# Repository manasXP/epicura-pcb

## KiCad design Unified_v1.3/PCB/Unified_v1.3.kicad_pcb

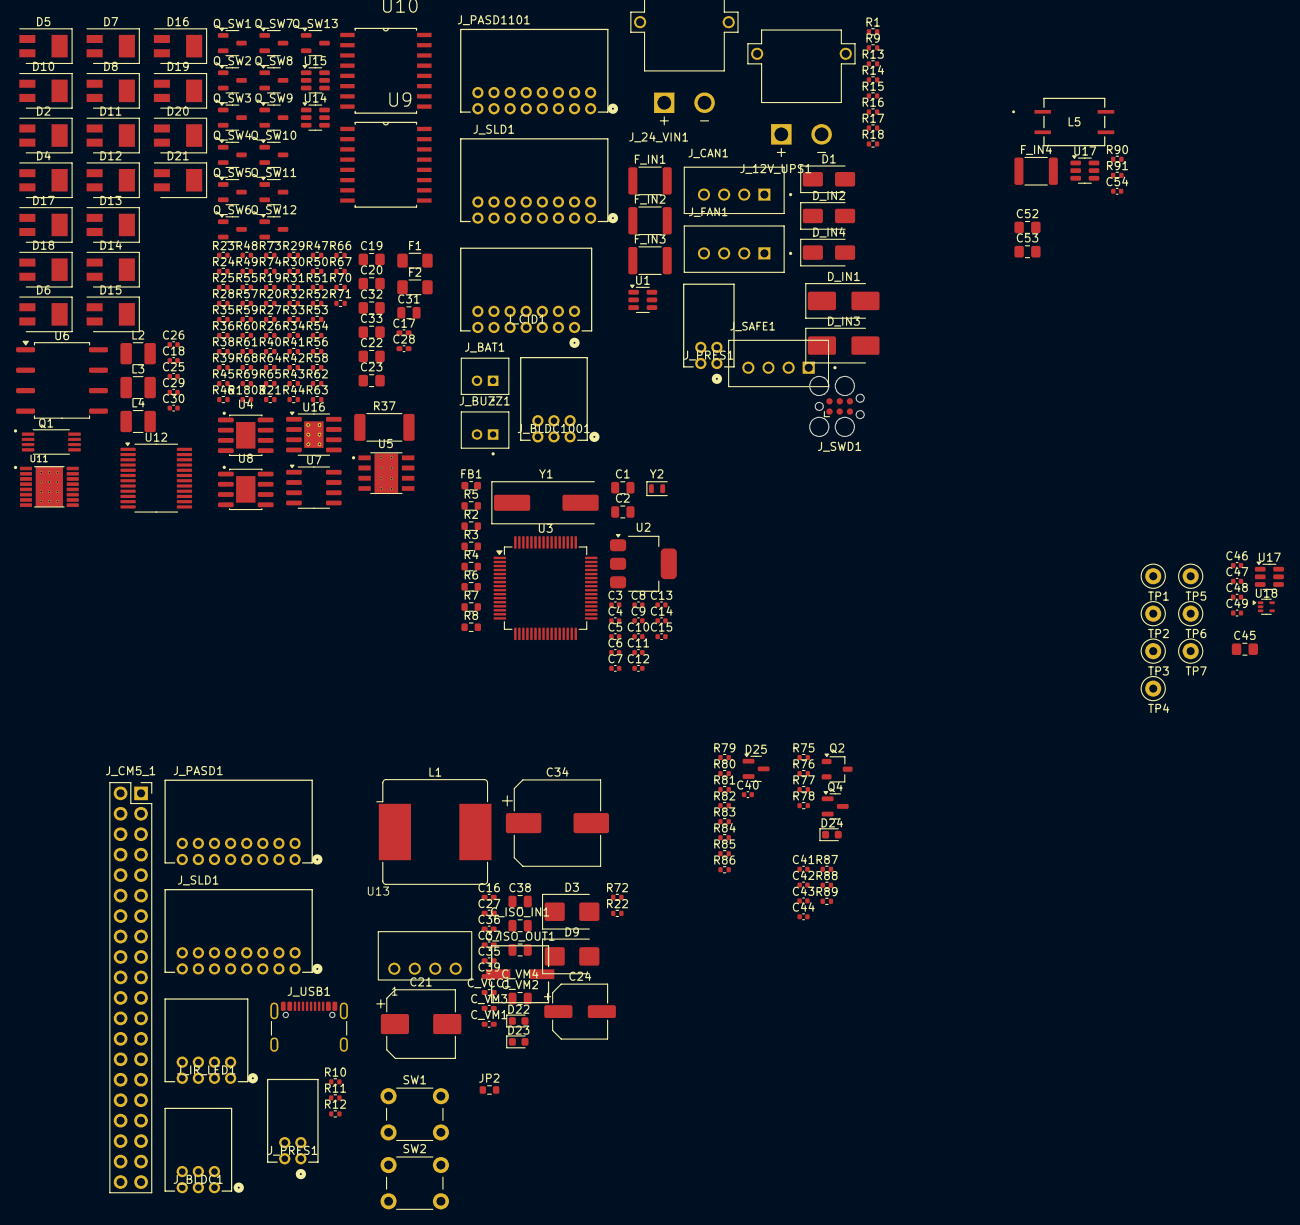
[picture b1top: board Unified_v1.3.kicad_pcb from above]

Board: 4 copper layers, 259 parts (0 on the bottom side), 185 nets, no tracks yet.

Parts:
C1, C2, C31: 10uF; C_0805_2012Metric
C3, C4, C5, C6, C7, C8, C9, C15, C29, C30, C40, C41, C42, C43, C54: 100nF; C_0402_1005Metric
C10: 1uF; C_0402_1005Metric
C11, C12: 18pF; C_0402_1005Metric
C13, C14: 6.8pF; C_0402_1005Metric
C16, C17, C27, C28, C35, C36, C37, C39: 100nF; C_0402_1005Metric_Pad0.74x0.62mm_HandSolder
C18: 2.2nF; C_0402_1005Metric
C19, C20, C32, C33, C45: 22uF@25V; C_0805_2012Metric_Pad1.18x1.45mm_HandSolder
C21: 100uF@25V; CP_Elec_8x10
C22, C23: 22uF@10V; C_0805_2012Metric_Pad1.18x1.45mm_HandSolder
C24: 220uF@10V; CP_Elec_6.3x7.7
C25: 22pF; C_0402_1005Metric
C26: 10nF; C_0402_1005Metric
C34: 470uF@35V; CP_Elec_10x12.5
C38: 22uF@16V; C_0805_2012Metric
C44: 4.7uF; C_0402_1005Metric
C46, C47, C48, C49: 100pF; C_0402_1005Metric
C52, C53: 10uF@50V; C_0805_2012Metric_Pad1.18x1.45mm_HandSolder
C_ISO_IN1: 4.7uF@16V; C_0805_2012Metric
C_ISO_OUT1: 10uF@16V; C_0805_2012Metric
C_VCC1: 100nF; C_0402_1005Metric_Pad0.74x0.62mm_HandSolder
C_VM1, C_VM3: 100nF; C_0402_1005Metric_Pad0.74x0.62mm_HandSolder
C_VM2: 10uF; C_0805_2012Metric
C_VM4: 100uF; 100uF_Wruth_CAP_WCAP-ASLI_06p3X07p7_WRE
D1: SS54; D_SMA
D2, D6, D7, D8, D11, D12, D13, D14, D15, D16, D17, D18, D19, D20, D21: SS14; D_SMB_Modified
D3: SMBJ12A; D_SMB
D4, D5, D10: SS34; D_SMB_Modified
D9: SMBJ6.5A; D_SMB
D22: LED_BLUE_STBY; D_0603_1608Metric
D23: LED_RED_CHRG; D_0603_1608Metric
D24: LED_GREEN_Status; D_0603_1608Metric
D25: CDSOT23-SM712; SOT-23
D_IN1, D_IN3: SMBJ24A _ 39.2 V; D_SMB_Handsoldering
D_IN2, D_IN4: SS54; D_SMA
F1, F2: 1.5A; R_1206_3216Metric_Pad1.30x1.75mm_HandSolder
FB1: 600R@100MHz; L_0603_1608Metric
F_IN1, F_IN2, F_IN4: 5A_PTC; R_1812_4532Metric
F_IN3: 500mA; R_1812_4532Metric
JP2: SWO_Jumper; R_0603_1608Metric
J_12V_UPS1, J_24_VIN1: XT30PW-M; AMASS_XT30PW-M
J_BAT1: B2B-PH-K-S; JST_B2B-PH-K-S
J_BLDC1, J_BLDC1001: DF11-6DP-2DS; CON6_2X3_RF_DF11
J_BUZZ1: B2B-PH-K-S; JST_B2B-PH-K-S
J_CAN1: B4B-XH-A; JST_B4B-XH-A
J_CID1: DF11-14DP-2DS; CON14_2X7_RF_DF11_HIR
J_CM5_1: Conn_02x20_Odd_Even; PinSocket_2x20_P2.54mm_Vertical
J_FAN1: B4B-XH-A; JST_B4B-XH-A
J_IR_LED1: DF11-8DP-2DS; CON8_2X4_RF_DF11
J_PASD1, J_PASD1101: DF11-16DP-2DS; CON16_2X8_RF_DF11
J_PRES1, J_PRES1#2: DF11-4DP-2DS; CON4_2X2_RF_DF11_HIR
J_SAFE1: B4B-XH-A; JST_B4B-XH-A
J_SLD1, J_SLD1#2: DF11-16DP-2DS; CON16_2X8_RF_DF11
J_SWD1: Conn_ARM_SWD_TagConnect_TC2030; Tag-Connect_TC2030-IDC-FP_2x03_P1.27mm_Vertical
J_USB1: USB_C_Receptacle_USB2.0_16P; USB_C_Receptacle_GCT_USB4105-xx-A_16P_TopMnt_Horizontal
L1: 10uH; L_Bourns_SRR1208_12.7x12.7mm
L2, L4: 33uH; L_1210_3225Metric_Pad1.42x2.65mm_HandSolder
L3: 22uH; L_1210_3225Metric_Pad1.42x2.65mm_HandSolder
L5: DR331-513AEE; IND_DR331-513AEE_BRN
Q1: FS8205A; FS8205A_SOP65P640X120-8N
Q2: SI2301-TP; TSOT-23
Q4: 2N7002; SOT-23
Q_SW1: 2N7002; SOT-23-3
Q_SW2, Q_SW3, Q_SW4, Q_SW5, Q_SW6, Q_SW7, Q_SW8, Q_SW9, Q_SW10, Q_SW11, Q_SW12, Q_SW13: IRLML6344; SOT-23-3
R1, R17, R18, R23, R28, R35, R39, R55, R65: 100K; R_0402_1005Metric
R2, R3: 4K7; R_0603_1608Metric
R4, R5, R6, R7, R8: 10K; R_0603_1608Metric
R9, R22, R27, R30, R32, R34, R38, R42, R44, R45, R50, R52, R54, R58, R63, R67, R71, R75, R77, R87, R88, R89, R90: 10K; R_0402_1005Metric
R10, R11, R12, R21, R29, R31, R33, R41, R43, R46, R47, R49, R51, R53, R56, R57, R59, R60, R61, R62, R66, R70, R72, R76, R79, R80, R81, R82, R83, R84, R85, R86, R91: 100R; R_0402_1005Metric
R13, R14: 5.1K; R_0402_1005Metric
R15, R16: 22R; R_0402_1005Metric
R19: 140K; R_0402_1005Metric
R20: 52.3K; R_0402_1005Metric
R24: 140KOhms; R_0402_1005Metric
R25: 10KOhms; R_0402_1005Metric
R26: 37.4K; R_0402_1005Metric
R36: 71.5K; R_0402_1005Metric
R37: 33m@3W; R_2512_6332Metric_Pad1.40x3.35mm_HandSolder
R40: 120R; R_0402_1005Metric
R48, R68, R69, R73: 1K; R_0402_1005Metric
R64: 732K; R_0402_1005Metric
R74, R1803: 2K; R_0402_1005Metric
R78: 330R; R_0402_1005Metric
SW1, SW2: SW_Push; SW_PUSH_6mm
TP1: PA2; TestPoint_Loop_D1.80mm_Drill1.0mm_Beaded
TP2: PA7; TestPoint_Loop_D1.80mm_Drill1.0mm_Beaded
TP3: PA9; TestPoint_Loop_D1.80mm_Drill1.0mm_Beaded
TP4: PC0; TestPoint_Loop_D1.80mm_Drill1.0mm_Beaded
TP5: PC1; TestPoint_Loop_D1.80mm_Drill1.0mm_Beaded
TP6: PC5; TestPoint_Loop_D1.80mm_Drill1.0mm_Beaded
TP7: PC13; TestPoint_Loop_D1.80mm_Drill1.0mm_Beaded
U1, U17: USBLC6-2SC6; SOT-23-6
U2: AMS1117-3.3; SOT-223-3_TabPin2
U3: STM32G474RETx; LQFP-64_10x10mm_P0.5mm
U4, U8: MP1584EN; MP1584EN_SOIC127P600X170-9N
U5: TPS54531DDA; TPS54531DDA_VREG_LM5017MR_NOPB
U6: ISO1050DUB; SOP-8_6.62x9.15mm_P2.54mm
U7: INA219AxD; SOIC-8_3.9x4.9mm_P1.27mm
U9, U10: PCF8574AT; SOIC127P1032X265-16N_PCF8574AT
U11: DRV8876PWPR
U12: TB6612FNG; SSOP-24_5.3x8.2mm_P0.65mm
U13: B0505S-1WR3; B0505S-1WR3_Footprint
U14: MT3608; SOT-23-6
U15: DW01A; SOT-23-6
U16: TP4056-42-ESOP8; SOIC-8-1EP_3.9x4.9mm_P1.27mm_EP2.41x3.3mm_ThermalVias
U17#2: TXB0101DBV; SOT-23-6
U18: TPD3E001DRLR; SOT-553
Y1: 8MHz; Crystal_SMD_HC49-SD
Y2: 32.768kHz; Crystal_SMD_2012-2Pin_2.0x1.2mm

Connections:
/24V_Divider: R1.2, R9.1, U3.13 (PA1)
/+3V3_OUT: C2.1, C3.1, C4.1, C5.1, C6.1, C7.1, C8.1, C27.2, C29.2, C35.2, C36.2, C37.1, C44.1, C54.2, C_VCC1.2, FB1.1, J_IR_LED1.3, J_PRES1.3, J_PRES1#2.3, J_SLD1#2.11, J_SWD1.1 (VCC), R2.1, R3.1, R5.1, R6.1, R7.2, R8.2, R45.2, R55.2, R86.1, R87.1, R88.1, R89.1, SW1.2, U2.2 (VO), U3.1 (VBAT), U3.16 (VDD), U3.32 (VDD), U3.48 (VDD), U3.64 (VDD), U6.1 (VCC1), U7.5 (VS), U9.1 (A0), U9.16 (VDD), U10.16 (VDD), U11.5 (VREF), U12.20 (VCC), U17.5 (VBUS), U17#2.1 (V_{CCA}), U18.5
/+5V_Detect: R17.1, R18.2, U3.17 (PA3)
/+5V_LED_RING: J_IR_LED1.7, Q2.3 (D), U17#2.6 (V_{CCB})
/+5V_Merger: C1.1, C_ISO_IN1.1, D1.1 (K), D2.1 (K), D18.1 (K), F_IN4.1, J_BUZZ1.1, Q2.2 (S), R75.1, U1.5 (VBUS), U2.3 (VI), U13.2 (Vin)
/+5V_USB: D1.2 (A), F_IN3.1, R17.2, R68.2, R69.1, U16.4 (V_{CC}), U16.8 (CE)
/+12V_IN: C45.1, D_IN3.1 (A1), D_IN4.1 (K), R19.1, U5.2 (VIN)
/+12V_Rail: C_VM1.2, C_VM2.2, C_VM3.2, C_VM4.1, D3.1 (K), F1.2, J_FAN1.1, J_FAN1.3, J_PASD1.1, J_PASD1.3, J_PASD1.5, J_PASD1.7, J_PASD1.9, J_PASD1.11, J_PASD1.13, J_SLD1#2.5, J_SLD1#2.7, U11.11 (VM), U12.13 (VM2), U12.14 (VM3), U12.24 (VM1)
/+24V_CC: C52.1, C53.1, J_CID1.12, R23.1, R35.1, R37.2, U4.7 (VIN), U7.7 (IN-), U8.7 (VIN)
/+24V_VIN: D_IN1.1 (A1), D_IN2.1 (K), J_BLDC1.1, R1.1, R37.1, U7.8 (IN+)
/BAT+: J_BAT1.1, L4.1, R72.2, R1803.1, U14.4 (EN), U14.5 (IN), U16.5 (BAT)
/BAT-: C39.1, J_BAT1.2, Q1.2, Q1.3, U15.6 (GND)
/BUZZ1_OUT: J_BUZZ1.2, Q_SW1.3 (D)
/CAN_H: L5.1, R40.2, U6.7 (CANH)
/CAN_L: L5.2, R40.1, U6.6 (CANL)
/CID1_EN: R12.1, U10.12 (P7)
/CID2_OUT1: J_CID1.7, U11.8 (OUT1)
/CID2_OUT2: J_CID1.8, U11.10 (OUT2)
/CM5_DE: JP2.2 (B), R91.2, U3.56 (PB3)
/Connector/12V_IN: J_PASD1101.1, J_PASD1101.3, J_PASD1101.5, J_PASD1101.7, J_PASD1101.9, J_PASD1101.11, J_PASD1101.13, J_SLD1.5, J_SLD1.7
/Connector/GPIO18: J_CM5_1.12, U17#2.3 (A)
/Connector/SWO: JP2.1 (A), J_SWD1.6 (SWO)
/Controller/+3V3_VDDA: C9.1, C10.1, FB1.2, U3.28 (VREF+), U3.29 (VDDA)
/Controller/Boot0: R4.2, SW1.1, U3.61 (PB8)
/Controller/HSE_IN: C12.1, U3.5 (PF0), Y1.2
/Controller/HSE_OUT: C11.1, U3.6 (PF1), Y1.1
/Controller/LSE_IN: C13.1, U3.3 (PC14), Y2.1
/Controller/LSE_OUT: C14.1, U3.4 (PC15), Y2.2
/Controller/PB6_CID1_HOME: C43.1, R6.2, R89.2
/DOUT_OIL: J_SLD1.14, R85.1, U3.52 (PC10)
/DOUT_WATER: J_SLD1.16, R84.1, U3.54 (PC12)
/Driver/+5V_FB: R20.1, R27.2, U5.5 (VSENSE)
/Driver/+5V_Isolated: C30.2, C31.2, C_ISO_OUT1.1, U6.8 (VCC2), U13.4 (Vout)
/Driver/+5V_SS: C26.2, U5.4 (SS)
/Driver/+6.5V_DCDC_FB: R36.2, R38.1, U8.4 (FB)
/Driver/+6.5V_OUT: D9.1 (K), F2.2
/Driver/+12V_DCDC_FB: R24.2, R25.1, U4.4 (FB)
/Driver/G_LED_Green: D24.2 (A), U9.6 (P2)
/Driver/G_LED_Ring: R76.2, U9.7 (P3)
/Driver/G_SLD_1: R51.2, U9.4 (P0)
/Driver/G_SLD_2: R53.2, U9.5 (P1)
/Driver/PASD_1: R29.2, U10.4 (P0)
/Driver/PASD_2: R31.2, U10.5 (P1)
/Driver/PASD_3: R33.2, U10.6 (P2)
/Driver/PASD_4: R41.2, U10.7 (P3)
/Driver/PASD_5: R43.2, U10.9 (P4)
/Driver/PASD_6: R47.2, U10.10 (P5)
/FAN1_OUT: D16.1 (K), J_FAN1.2, Q_SW10.3 (D)
/FAN2_OUT: D19.1 (K), J_FAN1.4, Q_SW11.3 (D)
/FDCAN1_RX: U3.58 (PB5), U6.2 (RXD)
/FDCAN1_TX: U3.59 (PB6), U6.3 (TXD)
/I2C1_SCL: J_IR_LED1.1, J_PRES1.1, J_PRES1#2.1, R2.2, U3.51 (PA15), U7.4 (SCL), U9.14 (SCL), U10.14 (SCL), U17.1 (I/O1)
/I2C1_SDA: J_IR_LED1.2, J_PRES1.2, J_PRES1#2.2, R3.2, U3.60 (PB7), U7.3 (SDA), U9.15 (SDA), U10.15 (SDA), U17.3 (I/O2)
/NRST: C15.1, J_SWD1.3 (~RESET), R8.1, SW2.1, U3.7 (PG10)
/PA0_PUMP_PWM: R66.2, U3.12 (PA0)
/PA4_EN: J_BLDC1001.4, R81.1, U3.18 (PA4), U18.4 (IO3)
/PA5_DIR: J_BLDC1001.5, R80.1, U3.19 (PA5), U18.2 (IO2)
/PA8_BLDC_PWM: J_BLDC1001.3, R79.1, U3.42 (PA8), U18.1 (IO1)
/PA10_CID1_PUL: R10.1, U3.44 (PA10)
/PASD1_D: D6.1 (K), J_PASD1.2, J_PASD1101.2, Q_SW2.3 (D)
/PASD2_D: D7.1 (K), J_PASD1.4, J_PASD1101.4, Q_SW3.3 (D)
/PASD3_D: D8.1 (K), J_PASD1.6, J_PASD1101.6, Q_SW4.3 (D)
/PASD4_D: D11.1 (K), J_PASD1.8, J_PASD1101.8, Q_SW5.3 (D)
/PASD5_D: D12.1 (K), J_PASD1.10, J_PASD1101.10, Q_SW6.3 (D)
/PASD6_D: D13.1 (K), J_PASD1.12, J_PASD1101.12, Q_SW7.3 (D)
/PASD7_D: D20.1 (K), J_PASD1.14, J_PASD1101.14, Q_SW12.3 (D)
/PB0_SAFETY_RELAY: R70.2, U3.24 (PB0)
/PB1_REED_SW: J_SAFE1.2, R5.2, U3.25 (PB1)
/PB2_E-STOP: C40.1, C41.1, J_SAFE1.3, R86.2, R87.2, U3.26 (PB2)
/PB4_CID1_DIR: R11.1, U3.57 (PB4)
/PB6_FAN1_PWM: R56.2, U3.20 (PA6)
/PB9_CID2_EN: R46.2, U3.62 (PB9)
/PB10_FAN2_PWM: R62.2, U3.30 (PB10)
/PB11_CID_HOME: J_CID1.9, U3.33 (PB11)
/PC2_CID2_DIR: R49.1, U3.10 (PC2)
/PC7_Buzzer_PWM: R21.2, U3.39 (PC7)
/PD2_CID2_HOME: C42.1, J_CID1.10, R7.1, R88.2, U3.55 (PD2)
/PUMP1_A01: J_SLD1.1, J_SLD1#2.1, U12.1 (AO1), U12.2 (AO1)
/PUMP1_A02: J_SLD1.2, J_SLD1#2.2, U12.5 (AO2), U12.6 (AO2)
/PUMP2_A01: J_SLD1.3, J_SLD1#2.3, U12.11 (BO1), U12.12 (BO1)
/PUMP2_A02: J_SLD1.4, J_SLD1#2.4, U12.7 (BO2), U12.8 (BO2)
/SAFETY_RELAY_D: D21.1 (K), J_SAFE1.1, Q_SW13.3 (D)
/SCLK_OIL: J_SLD1.13, R82.1, U3.41 (PC9)
/SCLK_WATER: J_SLD1.15, R83.1, U3.53 (PC11)
/SLD_OIL_DIR: R60.2, U3.22 (PC4)
/SLD_OIL_PWM: R57.2, U3.11 (PC3)
/SLD_WATER_DIR: R61.2, U3.38 (PC6)
/SLD_WATER_PWM: R59.1, U3.40 (PC8)
/SOL1_D: D14.1 (K), J_SLD1.6, J_SLD1#2.6, Q_SW8.3 (D)
/SOL2_D: D15.1 (K), J_SLD1.8, J_SLD1#2.8, Q_SW9.3 (D)
/SPI2_MISO: J_CM5_1.21, U3.36 (PB14)
/SPI2_MOSI: J_CM5_1.19, U3.37 (PB15)
/SPI2_NSS: J_CM5_1.24, U3.34 (PB12)
/SPI2_SCLK: J_CM5_1.23, U3.35 (PB13)
/SWCLK: J_SWD1.4 (SWCLK), U3.50 (PA14)
/SWDIO: J_SWD1.2 (SWDIO), U3.49 (PA13)
/USB_DM: U1.6 (I/O1), U3.45 (PA11)
/USB_DP: U1.4 (I/O2), U3.46 (PA12)
GND: C1.2, C2.2, C3.2, C4.2, C5.2, C6.2, C7.2, C8.2, C9.2, C10.2, C11.2, C12.2, C13.2, C14.2, C15.2, C19.2, C20.2, C21.2, C22.2, C23.2, C24.2, C25.2, C26.1, C27.1, C29.1, C32.2, C33.2, C34.2, C35.1, C36.1, C37.2, C38.1, C40.2, C41.2, C42.2, C43.2, C44.2, C45.2, C46.2, C47.1, C48.1, C49.2, C52.2, C53.2, C54.1, C_ISO_IN1.2, C_VCC1.1, C_VM1.1, C_VM2.1, C_VM3.1, C_VM4.2, D3.2 (A), D4.2 (A), D5.2 (A), D6.2 (A), D7.2 (A), D8.2 (A), D9.2 (A), D10.2 (A), D11.2 (A), D12.2 (A), D13.2 (A), D14.2 (A), D15.2 (A), D16.2 (A), D19.2 (A), D20.2 (A), D21.2 (A), D_IN1.2 (A2), D_IN3.2 (A2), J_BLDC1.2, J_BLDC1001.2, J_CID1.2, J_CID1.4, J_CID1.6, J_CID1.13, J_CID1.14, J_CM5_1.6, J_CM5_1.9, J_CM5_1.14, J_CM5_1.20, J_CM5_1.25, J_CM5_1.30, J_CM5_1.34, J_CM5_1.38, J_CM5_1.39, J_IR_LED1.4, J_IR_LED1.8, J_PASD1.15, J_PASD1.16, J_PASD1101.15, J_PASD1101.16, J_PRES1.4, J_PRES1#2.4, J_SAFE1.4, J_SLD1.11, J_SLD1.12, J_SLD1#2.12, J_SWD1.5 (GND), J_USB1.A1 (GND), J_USB1.A12 (GND), J_USB1.B1 (GND), J_USB1.B12 (GND), Q1.6, Q1.7, Q4.2 (S), Q_SW1.2 (S), Q_SW2.2 (S), Q_SW3.2 (S), Q_SW4.2 (S), Q_SW5.2 (S), Q_SW6.2 (S), Q_SW7.2 (S), Q_SW8.2 (S), Q_SW9.2 (S), Q_SW10.2 (S), Q_SW11.2 (S), Q_SW12.2 (S), Q_SW13.2 (S), R4.1, R9.2, R13.2, R14.1, R18.1, R22.2, R25.2, R26.1, R27.1, R28.2, R30.2, R32.2, R34.2, R38.2, R39.2, R42.2, R44.2, R48.2, R50.2, R52.2, R54.2, R58.2, R63.2, R65.2, R67.2, R71.2, R73.2, R74.1, R77.2, R78.1, R90.2, SW2.2, U1.2 (GND), U2.1 (GND), U3.15 (VSS), U3.27 (VSSA), U3.31 (VSS), U3.47 (VSS), U3.63 (VSS), U4.5 (GND), U4.9 (GND), U5.7 (GND), U6.4 (GND1), U7.1 (A1), U7.2 (A0), U7.6 (GND), U8.5 (GND), U8.9 (GND), U9.2 (A1), U9.3 (A2), U9.8 (VSS), U10.1 (A0), U10.2 (A1), U10.3 (A2), U10.8 (VSS), U11.9 (PGND), U11.15 (GND), U12.3 (PGND1), U12.4 (PGND1), U12.9 (PGND2), U12.10 (PGND2), U12.16 (BIN2), U12.18 (GND), U12.22 (AIN2), U13.1 (GND), U14.2 (GND), U16.1 (TEMP), U16.3 (GND), U16.9 (EPAD), U17.2 (GND), U17#2.2 (GND), U18.3
GND1: C30.1, C31.1, C_ISO_OUT1.2, D25.3 (common), J_CAN1.3, U6.5 (GND2), U13.3 (0V)
unnamed: C18.2, R26.2
unnamed: C19.1, C20.1, C21.1, F1.1, L2.2, R24.1
unnamed: C32.1, C33.1, C34.1, F2.1, L3.2, R36.1
unnamed: C22.1, C23.1, C24.1, D2.2 (A), L1.2, R20.2
unnamed: C16.2, D4.1 (K), L1.1, U5.8 (PH)
unnamed: C17.2, D5.1 (K), L2.1, U4.1 (SW)
unnamed: C28.2, D10.1 (K), L3.1, U8.1 (SW)
unnamed: D17.2 (A), L4.2, U14.1 (SW)
unnamed: C38.2, D17.1 (K), D18.2 (A), R64.1
unnamed: D22.2 (A), R68.1
unnamed: D22.1 (K), U16.6 (~STDBY)
unnamed: D23.2 (A), R69.2
unnamed: D23.1 (K), U16.7 (~CHRG)
unnamed: D24.1 (K), R78.2
unnamed: D25.1 (A1), J_CAN1.1, L5.4
unnamed: D25.2 (A2), J_CAN1.2, L5.3
unnamed: D_IN2.2 (A), F_IN1.1
unnamed: D_IN4.2 (A), F_IN2.1
unnamed: F_IN3.2, J_USB1.A4 (VBUS), J_USB1.A9 (VBUS), J_USB1.B4 (VBUS), J_USB1.B9 (VBUS)
unnamed: J_BLDC1.3, R79.2
unnamed: J_BLDC1.4, R81.2
unnamed: J_BLDC1.5, R80.2
unnamed: J_CID1.1, R10.2
unnamed: J_CID1.3, R11.2
unnamed: J_CID1.5, R12.2
unnamed: F_IN4.2, J_CM5_1.2, J_CM5_1.4
unnamed: J_CM5_1.7, R91.1
unnamed: J_IR_LED1.6, U17#2.4 (B)
unnamed: C46.1, J_SLD1#2.13, R82.2
unnamed: C49.1, J_SLD1#2.14, R85.2
unnamed: C47.2, J_SLD1#2.15, R83.2
unnamed: C48.2, J_SLD1#2.16, R84.2
unnamed: J_USB1.A5 (CC1), R13.1
unnamed: J_USB1.B5 (CC2), R14.2
unnamed: J_USB1.A6 (D+), J_USB1.B6 (D+), R16.1
unnamed: J_USB1.A7 (D-), J_USB1.B7 (D-), R15.2
unnamed: Q2.1 (G), Q4.3 (D), R75.2
unnamed: Q4.1 (G), R76.1, R77.1
unnamed: Q_SW1.1 (G), R21.1, R22.1
unnamed: Q_SW2.1 (G), R29.1, R30.1
unnamed: Q_SW3.1 (G), R31.1, R32.1
unnamed: Q_SW4.1 (G), R33.1, R34.1
unnamed: Q_SW5.1 (G), R41.1, R42.1
unnamed: Q_SW6.1 (G), R43.1, R44.1
unnamed: Q_SW7.1 (G), R47.1, R50.1
unnamed: Q_SW8.1 (G), R51.1, R52.1
unnamed: Q_SW9.1 (G), R53.1, R54.1
unnamed: Q_SW10.1 (G), R56.1, R58.1
unnamed: Q_SW11.1 (G), R62.1, R63.1
unnamed: Q_SW12.1 (G), R66.1, R67.1
unnamed: Q_SW13.1 (G), R70.1, R71.1
unnamed: R15.1, U1.1 (I/O1)
unnamed: R16.2, U1.3 (I/O2)
unnamed: TP1.1, U3.14 (PA2)
unnamed: TP2.1, U3.21 (PA7)
unnamed: TP3.1, U3.43 (PA9)
unnamed: TP4.1, U3.8 (PC0)
unnamed: TP5.1, U3.9 (PC1)
unnamed: TP6.1, U3.23 (PC5)
unnamed: TP7.1, U3.2 (PC13)
unnamed: C17.1, U4.8 (BST)
unnamed: R23.2, U4.2 (EN)
unnamed: R28.1, U4.6 (FREQ)
unnamed: C16.1, U5.1 (BOOT)
unnamed: C18.1, C25.1, U5.6 (COMP)
unnamed: R19.2, U5.3 (EN)
unnamed: C28.1, U8.8 (BST)
unnamed: R35.2, U8.2 (EN)
unnamed: R39.1, U8.6 (FREQ)
unnamed: R46.1, U11.1 (EN/IN1)
unnamed: R48.1, U11.6 (IPROPI)
unnamed: R45.1, U11.3 (NSLEEP)
unnamed: R49.2, U11.2 (PH/IN2)
unnamed: R60.1, U12.21 (AIN1)
unnamed: R61.1, U12.17 (BIN1)
unnamed: R57.1, U12.23 (PWMA)
unnamed: R59.2, U12.15 (PWMB)
unnamed: R55.1, U12.19 (STBY)
unnamed: R64.2, R65.1, U14.3 (FB)
unnamed: R73.1, U15.2 (CS)
unnamed: Q1.5, U15.3 (OC)
unnamed: Q1.4, U15.1 (OD)
unnamed: C39.2, R72.1, U15.5 (VCC)
unnamed: R74.2, U16.2 (PROG)
unnamed: R90.1, U17#2.5 (OE)
